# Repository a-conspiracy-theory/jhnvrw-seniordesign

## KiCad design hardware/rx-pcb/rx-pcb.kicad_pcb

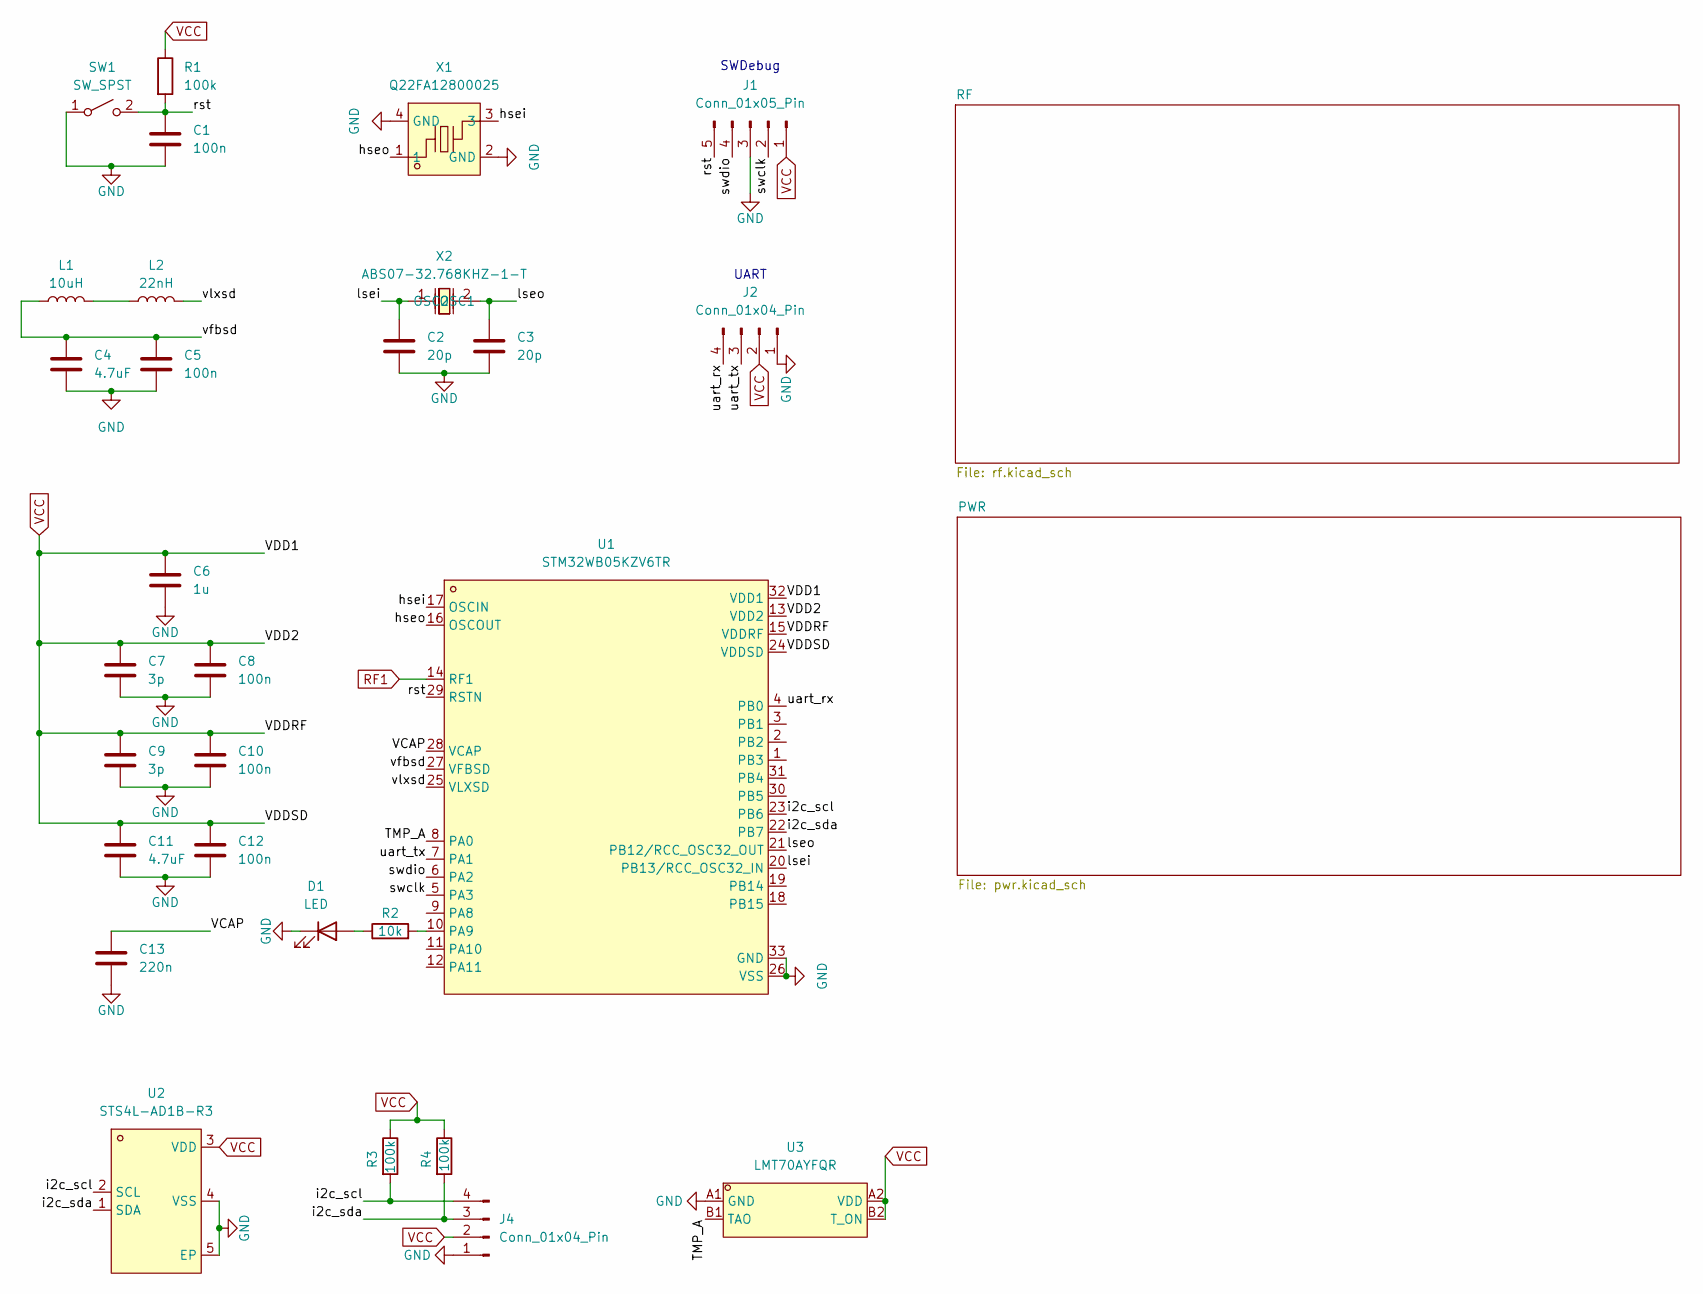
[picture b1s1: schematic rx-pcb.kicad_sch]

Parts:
C1, C5, C8, C10, C12: 100n; C_0805_2012Metric_Pad1.18x1.45mm_HandSolder
C2, C3: 20p; C_0805_2012Metric_Pad1.18x1.45mm_HandSolder
C4, C11: 4.7uF; C_0805_2012Metric_Pad1.18x1.45mm_HandSolder
C6: 1u; C_0805_2012Metric_Pad1.18x1.45mm_HandSolder
C7, C9: 3p; C_0805_2012Metric_Pad1.18x1.45mm_HandSolder
C13: 220n; C_0805_2012Metric_Pad1.18x1.45mm_HandSolder
D1: LED; LED_0805_2012Metric_Pad1.15x1.40mm_HandSolder
J1: Conn_01x05_Pin; PinHeader_1x05_P2.54mm_Vertical
J2, J4: Conn_01x04_Pin; PinHeader_1x04_P2.54mm_Vertical
L1: 10uH; L_0805_2012Metric_Pad1.05x1.20mm_HandSolder
L2: 22nH; L_0805_2012Metric_Pad1.05x1.20mm_HandSolder
R1, R3, R4: 100k; R_0805_2012Metric_Pad1.20x1.40mm_HandSolder
R2: 10k; R_0805_2012Metric_Pad1.20x1.40mm_HandSolder
SW1: SW_SPST; SW_PUSH_6mm
U1: STM32WB05KZV6TR; UFQFN-32_L5.0-W5.0-P0.50-TL-EP3.5; MPN STM32WB05KZV6TR; LCSC Part C28314403
U2: STS4L-AD1B-R3; DFN-4_L1.5-W1.5-P0.80-TL-EP; MPN STS4L-AD1B-R3; LCSC Part C41410764
U3: LMT70AYFQR; DSBGA-4_L0.8-W0.8-R2-C2-P0.40-BL; MPN LMT70AYFQR; LCSC Part C294608
X1: Q22FA12800025; CRYSTAL-SMD_4P-L2.0-W1.6-BL; MPN Q22FA12800025; LCSC Part C187794
X2: ABS07-32.768KHZ-1-T; OSC-SMD_2P-L3.2-W1.5; MPN ABS07-32.768KHz-1-T; LCSC Part C145140

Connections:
/TMP_A: U1.8 (PA0), U3.B1 (TAO)
/VCAP: C13.1, U1.28 (VCAP)
/hsei: U1.17 (OSCIN), X1.3
/hseo: U1.16 (OSCOUT), X1.1
/i2c_scl: J4.4, R3.2, U1.23 (PB6), U2.2 (SCL)
/i2c_sda: J4.3, R4.2, U1.22 (PB7), U2.1 (SDA)
/lsei: C2.1, U1.20 (PB13/RCC_OSC32_IN), X2.1 (OSC1)
/lseo: C3.1, U1.21 (PB12/RCC_OSC32_OUT), X2.2 (OSC2)
/rst: C1.1, J1.5, R1.2, SW1.2 (B), U1.29 (RSTN)
/swclk: J1.2, U1.5 (PA3)
/swdio: J1.4, U1.6 (PA2)
/uart_rx: J2.4, U1.4 (PB0)
/uart_tx: J2.3, U1.7 (PA1)
/vfbsd: C4.1, C5.1, L1.1, U1.27 (VFBSD)
/vlxsd: L2.2, U1.25 (VLXSD)
GND: C1.2, C2.2, C3.2, C4.2, C5.2, C6.2, C7.2, C8.2, C9.2, C10.2, C11.2, C12.2, C13.2, D1.1 (K), J1.3, J2.1, J4.1, SW1.1 (A), U1.26 (VSS), U1.33 (GND), U2.4 (VSS), U2.5 (EP), U3.A1 (GND), X1.2 (GND), X1.4 (GND); also elsewhere on the board
unnamed: D1.2 (A), R2.1
unnamed: L1.2, L2.1
unnamed: R2.2, U1.10 (PA9)
RF1: U1.14 (RF1); also elsewhere on the board
VCC: C6.1, C7.1, C8.1, C9.1, C10.1, C11.1, C12.1, J1.1, J2.2, J4.2, R1.1, R3.1, R4.1, U1.13 (VDD2), U1.15 (VDDRF), U1.24 (VDDSD), U1.32 (VDD1), U2.3 (VDD), U3.A2 (VDD), U3.B2 (T_ON); also elsewhere on the board

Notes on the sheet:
SWDebug
UART

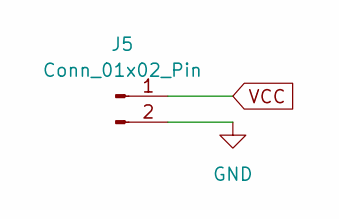
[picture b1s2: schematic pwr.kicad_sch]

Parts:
J5: Conn_01x02_Pin; PinHeader_1x02_P2.54mm_Vertical

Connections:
GND: J5.2; also elsewhere on the board
VCC: J5.1; also elsewhere on the board

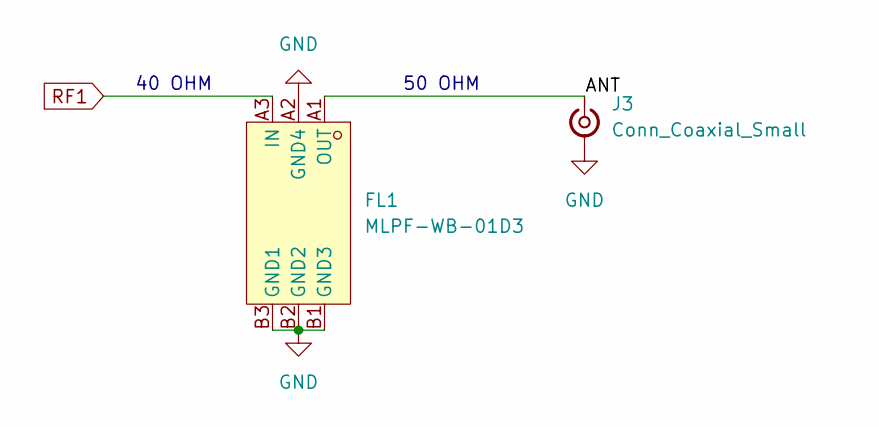
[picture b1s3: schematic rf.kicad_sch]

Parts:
FL1: MLPF-WB-01D3; BGA-6_L1.6-W1.0-R3-C2-P0.50-TL; MPN MLPF-WB-01D3; LCSC Part C5440144
J3: Conn_Coaxial_Small; SMA_Amphenol_901-143_Horizontal

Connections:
/RF/ANT: FL1.A1 (OUT), J3.1 (In)
GND: FL1.A2 (GND4), FL1.B1 (GND3), FL1.B2 (GND2), FL1.B3 (GND1), J3.2 (Ext); also elsewhere on the board
unnamed 18: FL1.A3 (IN); also elsewhere on the board

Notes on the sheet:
40 OHM
50 OHM

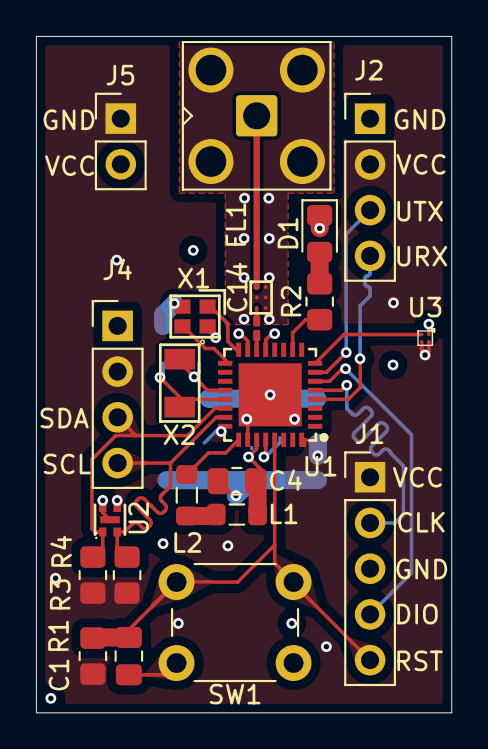
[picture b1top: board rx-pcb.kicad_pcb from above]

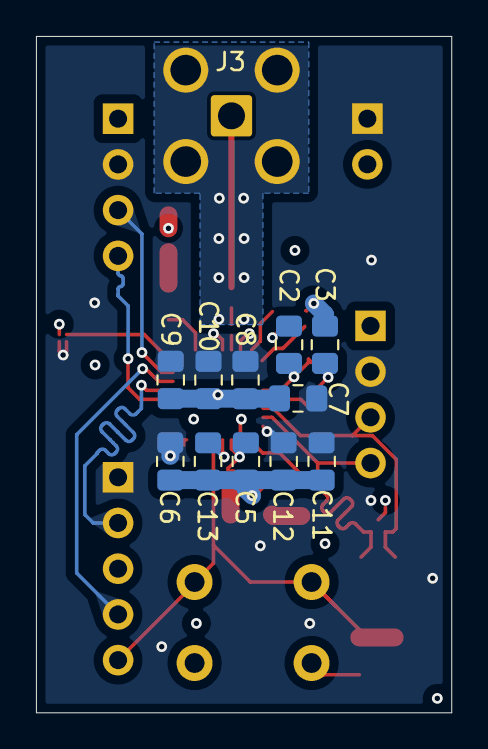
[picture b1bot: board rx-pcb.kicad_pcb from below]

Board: 4 copper layers, 23.1 x 37.6 mm, 33 parts (11 on the bottom side), 23 nets.

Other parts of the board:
C14: 20p; C_0201_0603Metric_Pad0.64x0.40mm_HandSolder

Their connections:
unnamed 18: C14.2; also elsewhere on the board
RF1: C14.1; also elsewhere on the board

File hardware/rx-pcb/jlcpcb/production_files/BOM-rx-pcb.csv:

Comment,Designator,Footprint,LCSC,Quantity
ABS07-32.768KHZ-1-T,X2,OSC-SMD_2P-L3.2-W1.5,C145140,1
LMT70AYFQR,U3,DSBGA-4_L0.8-W0.8-R2-C2-P0.40-BL,C294608,1
MLPF-WB-01D3,FL1,BGA-6_L1.6-W1.0-R3-C2-P0.50-TL,C5440144,1
Q22FA12800025,X1,CRYSTAL-SMD_4P-L2.0-W1.6-BL,C187794,1
STM32WB05KZV6TR,U1,UFQFN-32_L5.0-W5.0-P0.50-TL-EP3.5,C28314403,1
STS4L-AD1B-R3,U2,DFN-4_L1.5-W1.5-P0.80-TL-EP,C41410764,1
100k,R3,R_0805_2012Metric_Pad1.20x1.40mm_HandSolder,,1
22nH,L2,L_0805_2012Metric_Pad1.05x1.20mm_HandSolder,,1
100k,R1,R_0805_2012Metric_Pad1.20x1.40mm_HandSolder,,1
Conn_01x05_Pin,J1,PinHeader_1x05_P2.54mm_Vertical,,1
10uH,L1,L_0805_2012Metric_Pad1.05x1.20mm_HandSolder,,1
100n,C1,C_0805_2012Metric_Pad1.18x1.45mm_HandSolder,,1
4.7uF,C4,C_0805_2012Metric_Pad1.18x1.45mm_HandSolder,,1
Conn_01x04_Pin,J2,PinHeader_1x04_P2.54mm_Vertical,,1
Conn_01x04_Pin,J4,PinHeader_1x04_P2.54mm_Vertical,,1
LED,D1,LED_0805_2012Metric_Pad1.15x1.40mm_HandSolder,,1
Conn_Coaxial_Small,J3,SMA_Amphenol_901-143_Horizontal,,1
20p,C14,C_0201_0603Metric_Pad0.64x0.40mm_HandSolder,,1
Conn_01x02_Pin,J5,PinHeader_1x02_P2.54mm_Vertical,,1
100k,R4,R_0805_2012Metric_Pad1.20x1.40mm_HandSolder,,1
SW_SPST,SW1,SW_PUSH_6mm,,1
10k,R2,R_0805_2012Metric_Pad1.20x1.40mm_HandSolder,,1
220n,C13,C_0805_2012Metric_Pad1.18x1.45mm_HandSolder,,1
3p,C9,C_0805_2012Metric_Pad1.18x1.45mm_HandSolder,,1
1u,C6,C_0805_2012Metric_Pad1.18x1.45mm_HandSolder,,1
100n,C8,C_0805_2012Metric_Pad1.18x1.45mm_HandSolder,,1
100n,C5,C_0805_2012Metric_Pad1.18x1.45mm_HandSolder,,1
20p,C2,C_0805_2012Metric_Pad1.18x1.45mm_HandSolder,,1
4.7uF,C11,C_0805_2012Metric_Pad1.18x1.45mm_HandSolder,,1
100n,C12,C_0805_2012Metric_Pad1.18x1.45mm_HandSolder,,1
3p,C7,C_0805_2012Metric_Pad1.18x1.45mm_HandSolder,,1
100n,C10,C_0805_2012Metric_Pad1.18x1.45mm_HandSolder,,1
20p,C3,C_0805_2012Metric_Pad1.18x1.45mm_HandSolder,,1

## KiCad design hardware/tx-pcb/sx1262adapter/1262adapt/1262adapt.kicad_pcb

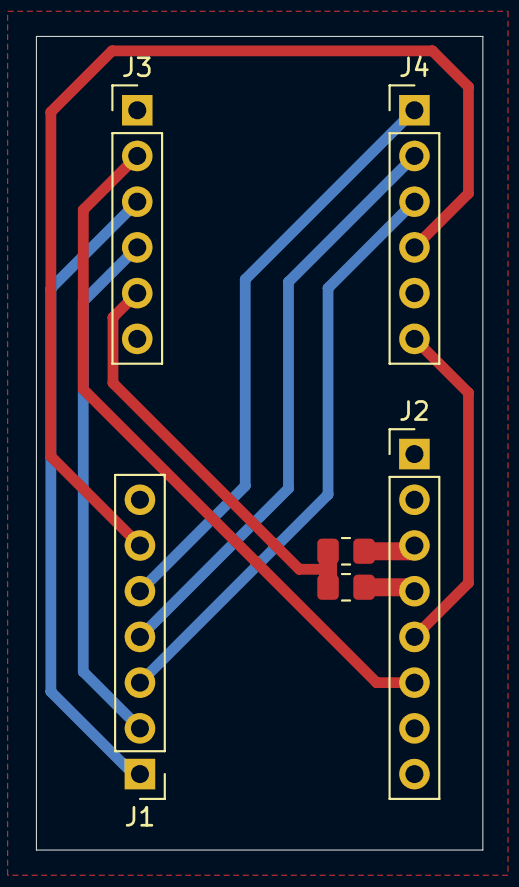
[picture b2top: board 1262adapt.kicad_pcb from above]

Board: 2 copper layers, 24.8 x 45.2 mm, 6 parts (0 on the bottom side), 12 nets.

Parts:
J1: Conn_To_J1; PinHeader_1x07_P2.54mm_Vertical
J2: Conn_To_J2; PinHeader_1x08_P2.54mm_Vertical
J3, J4: Conn_01x06; PinHeader_1x06_P2.54mm_Vertical
R1, R2: R; R_0805_2012Metric_Pad1.20x1.40mm_HandSolder

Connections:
/SPI_MISO: J1.3, J4.3
/SPI_MOSI: J1.4, J4.2
/SPI_SCK: J1.5, J4.1
/SX1262_BUSY: J1.1, J3.3
/SX1262_DIO1: J2.6, J3.2
/SX1262_DIO2: J2.5, J4.6
/SX1262_NSS: J1.6, J4.4
/SX1262_RFSW: J2.4, R1.1
/SX1262_RFSW#: J2.3, R2.2
/SX1262_RFSW_EN: J3.5, R1.2, R2.1
/SX1262_RST: J1.2, J3.4
GND: J1.7, J2.1, J2.2, J2.7, J4.5
